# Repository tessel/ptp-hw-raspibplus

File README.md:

**[UNMAINTAINED] This library does not have a maintainer. The source code and repository will be kept at this URL indefinitely. If you'd like to help maintain this codebase, create an issue on this repo explaining why you'd like to become a maintainer and tag @tessel/maintainers in the body.**

ptp-hw-raspibplus
==================
Hardware adaptor to allow Tessel modules to be used with a Raspberry Pi B+ in conjunction with the Portable Tessel Platform (PTP).

Designs in KiCad.

### License

Copyright 2014 Technical Machine, Inc.
CC-BY-SA

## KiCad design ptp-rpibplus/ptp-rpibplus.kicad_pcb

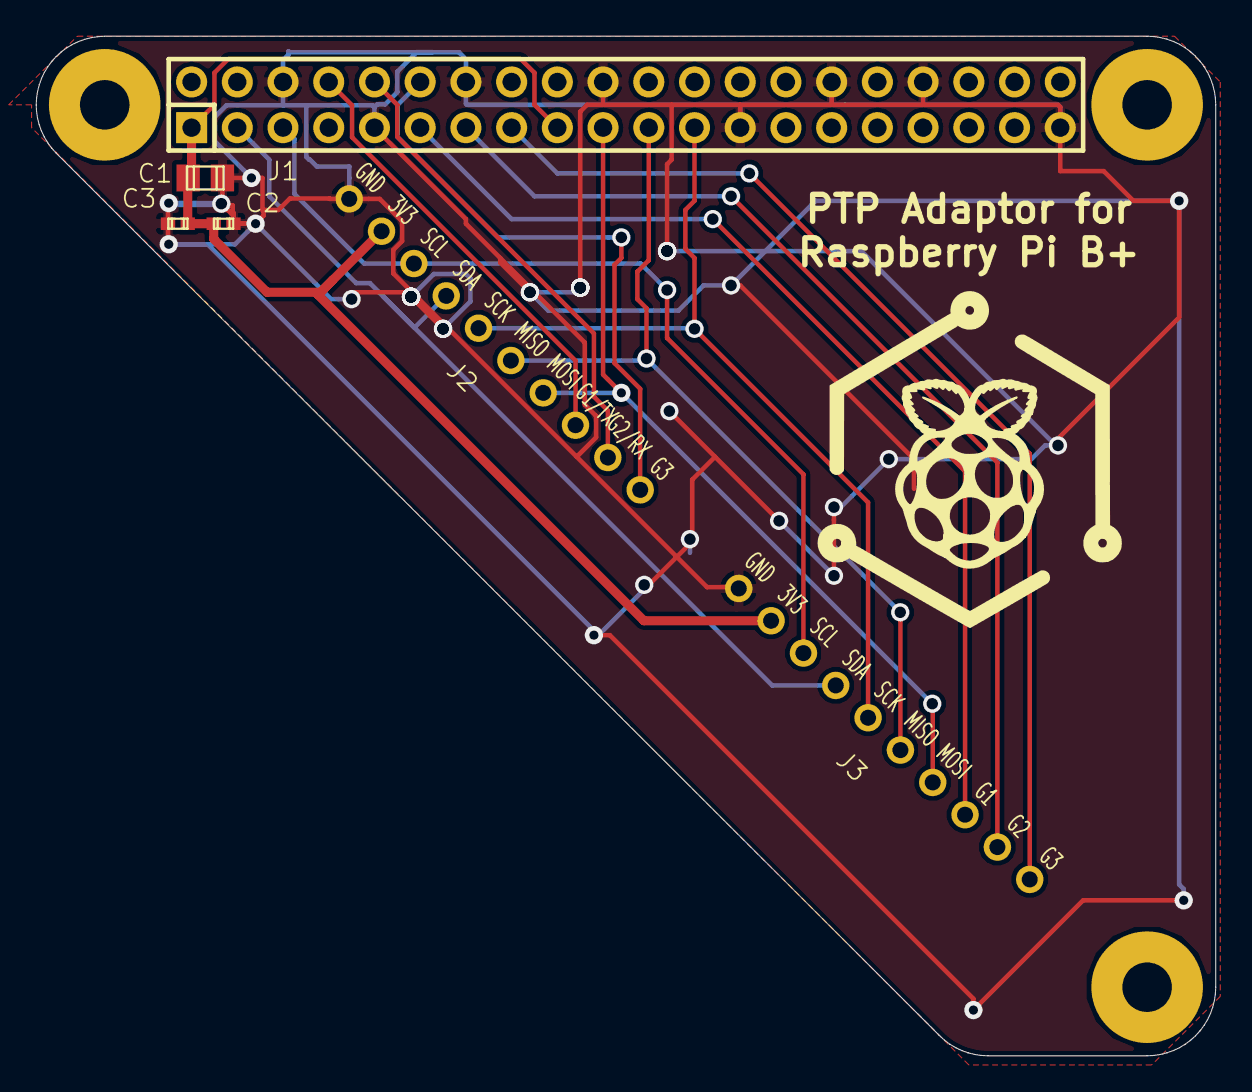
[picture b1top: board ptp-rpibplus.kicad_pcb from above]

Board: 2 copper layers, 65.5 x 56.6 mm, 10 parts (0 on the bottom side), 13 nets.

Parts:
C1: 10uF; c_0805
C2: 1uF; c_0402
C3: 100nF; c_0402
H1, H2, H3: HOLE; HOLE-2.75mm-6.2mm
J1: RASPI_B+; Pin_Header_Straight_2x20
J2, J3: MODULE_HEADER; MODULE_HEADER_TESSEL
SILK1: logo; PTP-RPI-LOGO

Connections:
3V3: C1.1, C2.1, C3.1, J1.1, J1.17, J2.2, J3.2
/A_G1/TX: J1.8, J2.8
/A_G2/RX: J1.10, J2.9
/A_G3: J1.12, J2.10
/B_G1/TX: J1.11, J3.8
/B_G2/RX: J1.13, J3.9
/B_G3: J1.15, J3.10
/MISO: J1.21, J2.6, J3.6
/MOSI: J1.19, J2.7, J3.7
/SCK: J1.23, J2.5, J3.5
/SCL: J1.5, J2.3, J3.3
/SDA: J1.3, J2.4, J3.4
GND: C1.2, C2.2, C3.2, J1.6, J1.9, J1.14, J1.20, J1.25, J1.30, J1.34, J1.39, J2.1, J3.1

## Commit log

2014-08-20 raspi module for ptp
2014-08-22 added silkscreen text
    fixed repo
    Create README.md
2014-09-05 update readme, license
2014-09-05 wipe for kicad
2014-09-05 started kicad project, schem
2014-09-05 parts in schematic, gotta do footprints
2014-09-05 schematic first pass
2014-09-05 netlist, annotation
2014-09-05 first pass component file
2014-09-05 board file exists, components are all on it...rpi silk is no good
2014-09-05 better silk for rpi header
2014-09-05 close to refresh
2014-09-05 note about 3.3 rail, updated silk
2014-09-05 ...at least the board has mount holes now
2014-09-05 how did the pcb files not get added?
2014-09-05 positioning things is hard
2014-09-05 started routing, decided to pursue parallel instead
2014-09-05 mostly happy. power and ground left.
2014-09-06 really really close
2014-09-06 stupid not-polygons are stupid
2014-09-06 silk tweaks to refdes
2014-09-06 10mil pour clear
2014-09-06 drc pass ...stupid vias
2014-09-06 pour tweaks
2014-09-06 gerbers
2014-09-06 project saved, closed, sent for review
2014-09-06 schem as postscript
2014-09-08 added ptp rpib+ logo, board dimensions, updated gerbers
2014-09-08 gerber zip
